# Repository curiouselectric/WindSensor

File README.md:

# WindSensor Overview
A DIY Wind sensor interface board.

This connects to various anemometers and wind vanes and provides a serial interface for averaged data from the pulses.

The problem with measuring wind anemometers and wind vane is that they constantly need to be checked. You need to know at all times when pulses have come in and which direction the wind vane is facing. This requires a bit of microcontroller time and processing. This unit is designed to solve that.
Wire up your vane and anemometer. Power the unit up. Then it will save the averaged data for you. You can then get hold of the data through serial requests and process as you need.

I wrote this to interface to an ESP32 data logger, which sleeps most of the time. It wakes up, talks to the wind sensor, gets the data it needs, then goes back to sleep, knowing the wind sensor is always monitoring.

It was designed as a relatively simple interface to remove the need for monitoring pulses and averaging them. 

## Wind Speed Measurements

The anemometer can either be a pulse output, NPN output or hall-effect output. The unit reads digital pulses, with circuitry on the unit converting the hall effect output to pulses. (Note: This unit cannot read 0-5V or analog output sensors).

The unit stores average wind speeds for 1 second, 10 second, 1 min, 10 min and 1 hour values. It also records the maximum and minimum wind speed.

The unit converts the pulses into a real wind speed using a y=mx+c linear conversion, where y is the wind speed and c is the number of pulses. m and c are stored in EEPROM and have default values of m=1 and c=0. These are floats and can be changed as required through the serial interface. Any updated values are stored in EEPROM. If the pulses are zero then the output is also zero (no matter what the y=mc+c function is). This stops a reading of 'c' when the pulse data is zero.

## Wind Vane Measurements

The wind vane input is analog. 

This can read either resistive wiper vanes or stepped resistive vanes. 

The stepped rsistive vanes have magnet reed switches which switch in and out different resistances. 
The resistance then tells us the direction. A pull up reistor is required in these situations.

The wind vane input can be 'trained'. So put the unit into vane training mode via the serial interface. This will run through N, NE, E, SE, S, SW, W, NW and you can hold the unit in the correct direction position and press the switch to store that data to memory. Once trained then the unit creates a buffer zone around each of the values and within the zone then the unit will record the correct direction.

Wind direction is slightly difficult to measure, as you cannot directly average the analog value (because of the potential rollover point from 360 degrees to 0 degrees point where the analog pin value rolls around from 1024 back to 0 - this means an average of a unit pointing just off north (i.e. one reading of 0 and one reading of 360) will give an average of (360+0)/2 = 180, which is south and totally wrong!). The code here creates 'bands', along with a 'rollover' band so that (for example) 900 to 1024 and 0 to 36 will be linked to North, so that the roll over point is handled as best as possible.

This unit will record the number of seconds the vane has been pointing in a certain direction. This means a 'wind rose' can relatively easily be created. This is stored and updated until it is directly reset. The unit will also return the instantaneous direction, if that is needed.

There are two mode of operation, depending upon your use case (please see the firmware for more detailled information about the available serial commands):

## Response Mode

In this mode then the unit responds to serial requests made. You ask the sensor for data and this is returned. It never sends anything unless asked. 

## Broadcast Mode

In this mode then the unit regularly sends data via the serial connunication. It will send the averaged data for (0) 1 second, (1) 10 second, (2) 1 min, (3) 10 min and (4) 1 hour averaged data. If this is set to (5) then the unit does not send any data. The send mdoe is stored in EEPROM, so it will start sending data again even if power is lost.

Boradcast mode works well if the logger is always listening and you only have one sensor in range. If more than one sensor is in range then the data will clash and potentially cause issues, in which case use Response mode.

The two modes work together - you can have the unit sending regular data and also responding to requests.

It runs on an ATMega328 running at 8MHz (external crystal) with selectable baud serial (up to 57600). It comes pre-programmed, but code can be uploaded via the Arduino IDE, using the MiniCore board add-on. See firmware for more details.

# Hardware

The PCB was designed in KiCAD and is available here. A small PCB has been designed.
There is one reset switch, one user input switch and one LED output.

Both inputs for the wind vane and anemometer are buffered with an op-amp and also have 5.1V zener protection. The anemometer input compares the input with a low voltage level to create a pulse from a hall-effect (which output a sine-wave like signal). This also works as a pull-down pulse sensor, which works with NPN and switch output anemometers.

## Anemometers Tested:

Anemometer Name      | Link   | Type   | m Value   | c Value
---------------------|----------|---------|----------|----------
Vector Insrutments NRG #40C | [https://www.nrgsystems.com/products/met-sensors/detail/40c-anemometer](https://www.nrgsystems.com/products/met-sensors/detail/40c-anemometer) | Hall-effect  | 0.765 for m/s | 0.35 for m/s
Maplin Anemometer (low cost) | [https://www.ebay.co.uk/itm/274338314354](https://www.ebay.co.uk/itm/274338314354) | Reed-switch pulse | 0.7 for m/s | 0 for m/s
Curios Electric PR-3000-FS-NPN| [https://www.curiouselectric.co.uk/collections/featured/products/anemometer-for-wind-speed-measurements](https://www.curiouselectric.co.uk/collections/featured/products/anemometer-for-wind-speed-measurements) | NPN Pulse | 0.0875 for m/s | 0 for m/s
Pro-D Anemometer/Vane combination| [https://cdn.shopify.com/s/files/1/0115/9192/files/Pro-D_Anemometer_Specs_v2.docx.pdf](https://cdn.shopify.com/s/files/1/0115/9192/files/Pro-D_Anemometer_Specs_v2.docx.pdf) | Magnetic pulse | 1.006 for m/s | 0 for m/s

## Wind Vanes Tested:

Wind Vane Name      |   Link   |  Type
---------------------|----------|-----------
Maplin Vane | No Link |  Switched resistive
Pro-D Anemometer/Vane combination| [https://cdn.shopify.com/s/files/1/0115/9192/files/Pro-D_Anemometer_Specs_v2.docx.pdf](https://cdn.shopify.com/s/files/1/0115/9192/files/Pro-D_Anemometer_Specs_v2.docx.pdf) | 20k resistive
Curios Electric ZTS-3000-TR-FSJT-NPN | [https://www.curiouselectric.co.uk/collections/featured/products/wind-vane-for-wind-direction-measurements](https://www.curiouselectric.co.uk/collections/featured/products/wind-vane-for-wind-direction-measurements) | 0-3.3V output

## Board ID Number

Each unit can have a unique ID (using a solder pad for 0-7 values), so multiple units can be added to a serial bus, if needed. The defalt is 0.

# Firmware

This uses an ATMega328 running at 8MHz with 3.3v or 5V supply.

The firmware used in this project is available in this github repository:

[https://github.com/curiouselectric/SensorInterfaceFirmware](https://github.com/curiouselectric/SensorInterfaceFirmware) 

Please follow the information within that repository for the serial commands and firmware information.

# Overview of Connections

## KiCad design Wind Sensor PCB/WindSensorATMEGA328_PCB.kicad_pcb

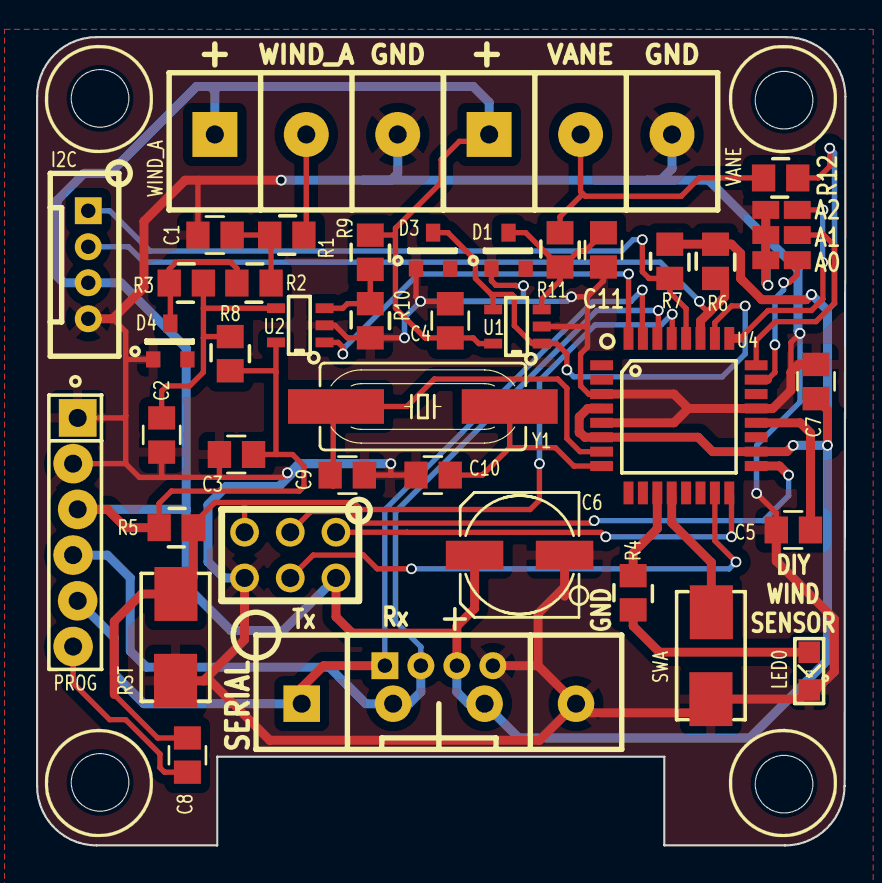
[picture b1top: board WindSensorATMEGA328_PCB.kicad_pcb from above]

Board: 2 copper layers, 44.9 x 44.9 mm, 42 parts (1 on the bottom side), 29 nets.

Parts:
C1, C3, C4, C5, C7, C8, C11: 100n; SM_C_0805
C2: 22n; SM_C_0805
C6: 100u; SM_6.3x7.7
C9, C10: 22p; SM_C_0805
D1, D4: 3V3_Zener; SOT23_ZENER
D2: LED0; SM0805_LED
D3: 5V1_Zener; SOT23_ZENER
P2: SERIAL; SIL-4_Grove_SCREW
P3: ID; SM_6pad_3W_SOLDER
P4: ISP; ISP_3x2
P5: LOGO2; TCEC_Words_13mm
P6: PCB; PCB_45_45_Cut_Out_Solar_Sensor_2
P8: VANE; SIL-3_screw_terminal
P9: PROG; TH_6x1_FTDI
P10: I2C; SIL-4_Grove_Not_Labelled
P11: WIND_A; SIL-3_screw_terminal
R1, R5, R10, R11, R12: 10k; SM0805
R2, R3, R6, R7: 4k7; SM0805
R4: 470; SM0805
R8: 470k; SM0805
R9: 100k; SM0805
SW1: SWA; SMD_SW_6x3_5
SW2: RST; SMD_SW_6x3_5
U1, U2: TSV911xxLx; SM_SOT-23-5
U4: ATmega328P-AU; TQFP32-08
Y1: 8MHz_XTAL; SM-crystal-HC49UP

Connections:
/ATMega328/A0: P3.1, U4.23 (PC0)
/ATMega328/A1: P3.3, U4.24 (PC1)
/ATMega328/A2: P3.5, U4.25 (PC2)
/ATMega328/D7: R4.1, U4.11 (PD7)
/ATMega328/D8: SW1.1, U4.12 (PB0)
/ATMega328/DTR: C8.1, P9.6
/ATMega328/MISO: P4.1, U4.16 (PB4)
/ATMega328/MOSI: P4.4, U4.15 (PB3)
/ATMega328/RESET: C8.2, P4.5, R5.2, SW2.1, U4.29 (~RESET/PC6)
/ATMega328/SCLK: P4.3, U4.17 (PB5)
/Hall_to_Freq/WIND_A_SIG: P11.2, R1.2
/I2C_CLK: P10.1, R7.2, U4.28 (PC5)
/I2C_SDA: P10.2, R6.2, U4.27 (PC4)
/Rx: P2.2, P9.4, U4.30 (PD0)
/Tx: P2.1, P9.5, U4.31 (PD1)
/WIND_FREQ: U2.1, U4.32 (PD2)
/WIND_VANE: D3.2 (K), U1.1, U1.4 (-), U4.26 (PC3)
/Wind_Vane/WIND_V_SIG: P8.2, R11.2, R12.2
GND: C1.1, C2.2, C3.1, C4.1, C5.1, C6.2, C7.1, C9.1, C10.1, C11.1, D1.1 (A), D2.1 (K), D3.1 (A), D4.1 (A), P2.4, P3.2, P3.4, P3.6, P4.6, P8.3, P9.1, P9.2, P10.4, P11.3, R10.1, SW1.2, SW2.2, U1.2 (V-), U2.2 (V-), U4.3 (GND), U4.5 (GND), U4.21 (GND)
unnamed: C1.2, R1.1, R2.2
unnamed: C11.2, D1.2 (K), R11.1, U1.3 (+)
unnamed: D2.2 (A), R4.2
unnamed: D4.2 (K), R2.1, R3.2
unnamed: R9.2, R10.2, U2.3 (+)
unnamed: C2.1, R3.1, R8.2, U2.4 (-)
unnamed: C5.2, U4.20 (AREF)
unnamed: C9.2, U4.7 (XTAL1/PB6), Y1.1
unnamed: C10.2, U4.8 (XTAL2/PB7), Y1.2
VCC: C3.2, C4.2, C6.1, C7.2, P2.3, P4.2, P8.1, P9.3, P10.3, P11.1, R5.1, R6.1, R7.1, R8.1, R9.1, R12.1, U1.5 (V+), U2.5 (V+), U4.4 (VCC), U4.6 (VCC), U4.18 (AVCC)

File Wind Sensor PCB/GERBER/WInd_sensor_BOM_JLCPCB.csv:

Comment,Designator,Footprint,LCSC Part Number
22p,"C9,C10",REInnovationFootprint:SM_C_0805,C1804
22n,C2,REInnovationFootprint:SM_C_0805,C1804
100n,"C3,C4,C5,C7,C8",REInnovationFootprint:SM_C_0805,C49678
100u,C6,REInnovationFootprint:SM_6.3x7.7,C164071
5V1_Zener,"D1,D3",REInnovationFootprint:SOT23_ZENER,C131770
LED0,D2,REInnovationFootprint:SM0805_LED,C2296
3V3_Zener,D4,REInnovationFootprint:SOT23_ZENER,C130247
I2C,P10,REInnovationFootprint:SIL-4_Grove_Not_Labelled,
WIND_A,P11,REInnovationFootprint:SIL-3_screw_terminal,
SERIAL,P2,REInnovationFootprint:SIL-4_Grove_SCREW,
ID,P3,REInnovationFootprint:SM_6pad_3W_SOLDER,
ISP,P4,REInnovationFootprint:ISP_3x2,
LOGO2,P5,CuriousElectric3:TCEC_Words_13mm,
PCB,P6,REInnovationFootprint:PCB_45_45_Cut_Out_Solar_Sensor,
ENC,P7,,
VANE,P8,REInnovationFootprint:SIL-3_screw_terminal,
PROG,P9,REInnovationFootprint:TH_6x1_FTDI,
4M7,R11,REInnovationFootprint:SM0805,C17674
4k7,"R2,R3",REInnovationFootprint:SM0805, C17673
470,R4,REInnovationFootprint:SM0805,C17710
10k,"R5,R6,R7,R10",REInnovationFootprint:SM0805,C17673
100k,"R8,R9",REInnovationFootprint:SM0805,C17407
SWA,SW1,REInnovationFootprint:SMD_SW_6x3_5,C412368
RST,SW2,REInnovationFootprint:SMD_SW_6x3_5,C412368
TSV911xxLx,"U1,U2",REInnovationFootprint:SM_SOT-23-5,C361052
ATmega328P-AU,U4,REInnovationFootprint:TQFP32-08,C14877
8MHz_XTAL,Y1,REInnovationFootprint:SM-crystal-HC49UP,C12674

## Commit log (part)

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2021-07-16 Large initial commit. From SolarSensor
2021-07-19 Initial design for PCB and schematic
2021-07-19 updated PCB
2021-07-19 u[dated PCB
2021-07-19 Updated PCB
    Version 1 of the PCB with ATMEGA328 used...
2021-10-17 large code update
2021-10-17 updated to do correct vane direction
2021-10-21 Updated to work as wind sensor
    Added wind vane calculations
    Added wind speed calculations
    Added conversion store
2021-10-22 Update ATMega328_Wind_Sensor_Averaging.ino
    Added correct reset
    Added set wind speed to zero if no pulses
2021-10-22 Create Wind Sensor Instructions.docx
    added instructions
2021-10-23 added images
2021-10-24 Updated code to act as broadcast
2021-10-26 updated images and code and instructions
2021-10-27 updated code with broadcast mode fix
2021-10-28 Added a display version of the firmware
2022-04-17 updated instructions
2024-08-07 Update of PCB to add LPF on inputs
2024-09-13 Update README.md
    added CRC check info
2024-09-13 Added CRC check to firmware
2024-10-30 Large update - firmware and PCB design. V2
2024-11-12 Update README.md
    Added to wind anemometer conversion
2024-11-13 updated wind vane input
2024-11-20 Changed to 5V6 zener on all protection
2024-11-20 updated instructions and schematic files
2025-03-10 updated PCB for kicad 8
2025-12-23 Small changes to main code
    Also added development folder for firmware to try to sort out no 'String' code version.
2026-03-13 removed firmware
    New firmware is in the sensor board interface so can be kept updated
2026-06-15 added wind vane and Anemometer datasheets
